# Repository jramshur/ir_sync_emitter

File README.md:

# Description

The IR Sync Emitter is a device that produces a high intensity IR pulse when a TTL type signal is received on its input. The duration of the pulse is determined by the duration of the TTL input.

It was designed to be used as a means of wirelessly synchronizing rack mounted electrophysiology equipment with the [SRD brain computer interface](http://github.com/jramshur/srd_gui). However, it is not limited to this use.

**Warning:** Use caution when operating this device. Intense IR light can cause retinal damage.

## PCB

You can order the PCB from Oshpark.com [here](http://oshpark.com/shared_projects/bxmRX5iz).

## Schematic

## Photo

## BOM

comming soon ...

| Part | Value | MF | Package | Description |
|------|-------|----|---------|-------------|
| LEDx |  |  | 0603 | LED |
| Qx | MTD8000M3B-T | Marktech Optoelectronics | TH | IR Phototransistor |

## Contact Info

John T. Ramshur, PhD  
jramshur@gmail.com  
LinkedIn: [http://www.linkedin.com/in/johnramshur](http://www.linkedin.com/in/johnramshur)  
Blog: [http://www.johnramshur.com](http://www.johnramshur.com)

## License

GNU General Public License 3.0

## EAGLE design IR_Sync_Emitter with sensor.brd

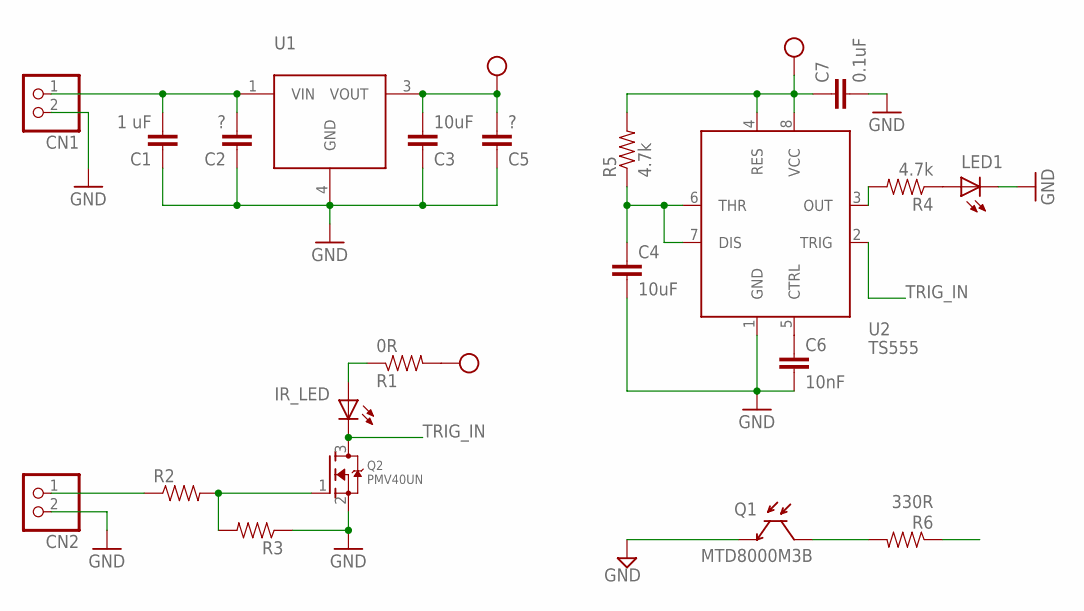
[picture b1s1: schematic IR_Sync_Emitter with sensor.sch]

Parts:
C1: 1 uF; CAPC2012X100N
C2, C5: ?; CAPC2012X100N
C3, C4: 10uF; CAPC2012X100N
C6: 10nF; CAPC2012X100N
C7: 0.1uF; CAPC2012X100N
CN1, CN2: JST_2PIN-SMT-RA; JST-PH-2-SMT-RA
IR_LED: LEDIR_SMT16.2X11.2; LED_SMT6.2X11.2
LED1: LED0603; CHIPLED_0603
Q1: MTD8000M3B; MTD8000M3B-T
Q2: PMV40UN; SOT23
R1: 0R; RESC3116X65N
R2, R3: RR0805-N; RESC2012X60N
R4, R5: 4.7k; RESC2012X60N
R6: 330R; RESC2012X60N
U1: LM2931_FIXED; DPAK
U2: TS555; SO08

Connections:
GND: C1.1, C2.1, C3.1, C4.2, C5.1, C6.2, C7.2, CN1.2 (1), CN2.2 (1), LED1.C, Q1.E, Q2.2 (S), R3.1, U1.4 (GND), U2.1 (GND)
unnamed: LED1.A, R4.1
unnamed: Q2.1 (G), R2.2, R3.2
unnamed: C1.2, C2.2, CN1.1 (2), U1.1 (VIN)
unnamed: IR_LED.A, R1.1
unnamed: Q1.C, R6.2
unnamed: CN2.1 (2), R2.1
unnamed: R4.2, U2.3 (OUT)
unnamed: C4.1, R5.1, U2.6 (THR), U2.7 (DIS)
unnamed: C6.1, U2.5 (CTRL)
TRIG_IN: IR_LED.C, Q2.3 (D), U2.2 (TRIG)
VDD: C3.2, C5.2, C7.1, R1.2, R5.2, U1.3 (VOUT), U2.4 (RES), U2.8 (VCC)

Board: 2 copper layers, 21 parts (12 on the bottom side), 12 nets, no tracks yet.

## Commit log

2015-09-15 :neckbeard: Added .gitattributes & .gitignore files
2015-09-15 added images and updated readme
2015-09-15 readme

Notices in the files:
parts and their libraries:
SparkFun-PowerIC: Licensing: CC v3.0 Share-Alike You are welcome to use this library for commercial purposes.
